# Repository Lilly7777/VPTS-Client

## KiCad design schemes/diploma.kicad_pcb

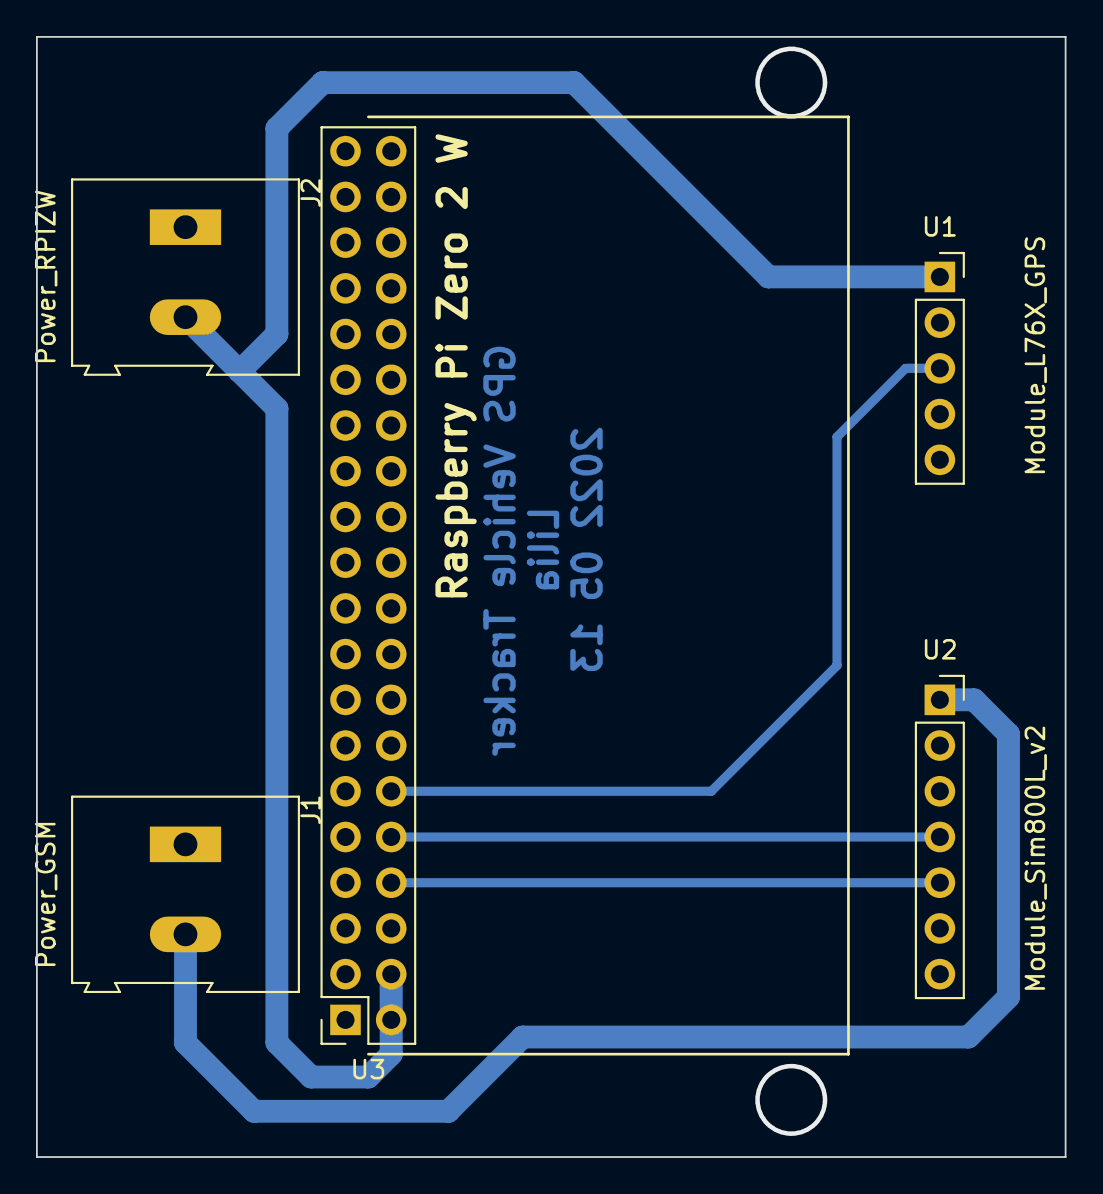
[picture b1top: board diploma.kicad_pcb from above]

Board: 2 copper layers, 57.2 x 62.2 mm, 5 parts (0 on the bottom side), 6 nets.

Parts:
J1: Power_GSM; TerminalBlock_Altech_AK300-2_P5.00mm
J2: Power_RPIZW; TerminalBlock_Altech_AK300-2_P5.00mm
U1: Module_L76X_GPS; PinSocket_1x05_P2.54mm_Vertical
U2: Module_Sim800L_v2; PinSocket_1x07_P2.54mm_Vertical
U3: 40HAT; PinSocket_2x20_P2.54mm_Vertical

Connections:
+5V: J2.2, U1.1 (Vcc_5V), U3.2 (P5V), U3.4 (P5V)
/bcm14: U2.5 (RxD), U3.8 (BCM14)
/bcm15: U2.4 (TxD), U3.10 (BCM15)
GND: J1.1, J2.1, U1.2 (GND), U2.2 (GND), U2.6 (GND), U3.6 (GND), U3.9 (GND), U3.14 (GND), U3.20 (GND), U3.25 (GND), U3.30 (GND), U3.34 (GND), U3.39 (GND)
unnamed: U1.3 (TxD), U3.12 (BCM18)
VBUS: J1.2, U2.1 (Vcc_5V)

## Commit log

2022-03-20 [Add] MQTT paho client who connects the broker
2022-03-20 [Add] Structure for GPS record
2022-03-20 [Add] Serial communication of GPS module and retrieval of coordinates
2022-03-24 [Remove] Removed gps folder
2022-03-24 [Update] Removed unnecessary imports and casting string variables to integers.
2022-03-24 [Update] Moved files to main folder
2022-03-30 [Update] Added pigpio library for second UART
2022-05-21 [Add] KiCad schemes
